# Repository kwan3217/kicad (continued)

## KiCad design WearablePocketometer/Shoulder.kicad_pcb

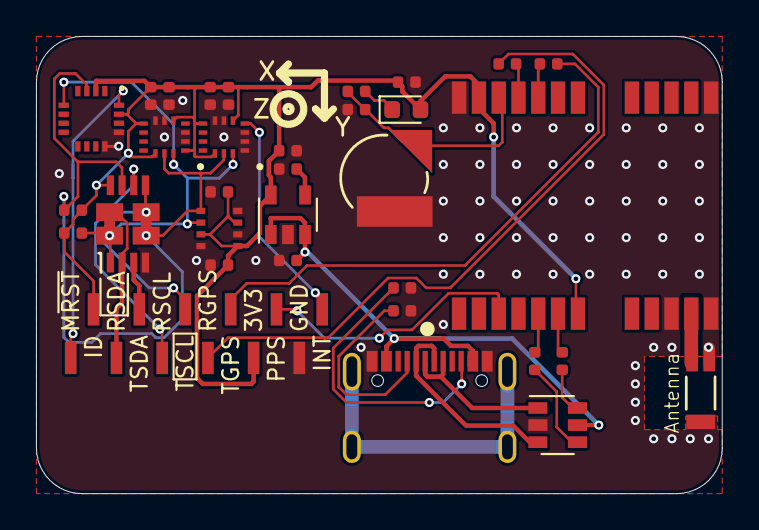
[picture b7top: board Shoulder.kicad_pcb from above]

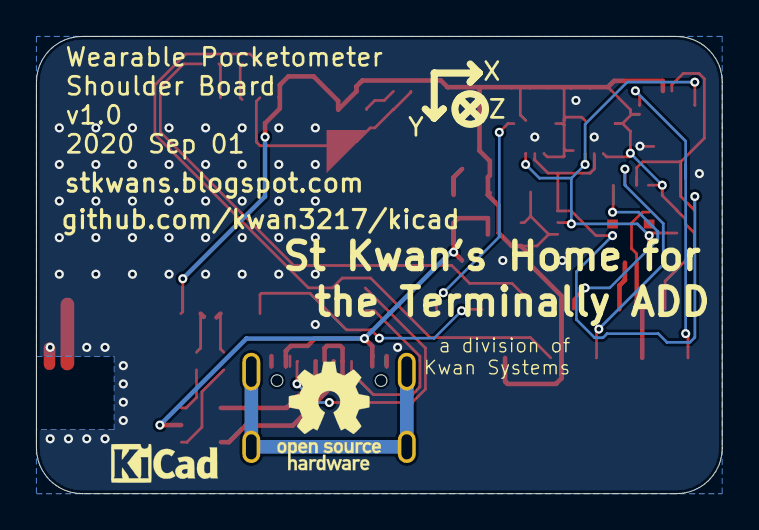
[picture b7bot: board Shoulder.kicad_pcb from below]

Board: 2 copper layers, 38.1 x 25.4 mm, 39 parts (3 on the bottom side), 28 nets.

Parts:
B601: ML414H; Coin_Cell_ML414H
C305, C308, C406, C408, C505, C508, C804: 100nF; C_0402_1005Metric
C601, C801: 1uF; C_0402_1005Metric
C805: 2.2uF; C_0402_1005Metric
D601: 0.5A/40V/420mV; D_0603_1608Metric
G504: Axis
G901: DesignedWithKicad; Symbol_KiCAD-Logo_CopperAndSilkScreenTop_small
G902: KwanSystems; StKwansSoldermask
G903: OSHW; OSHW-Logo_5.7x6mm_SilkScreen
J201, J207: SolderJumper_2_Open; SolderJumper-2_Bridged
J202: Conn_02x06_Male; PinSocket_1x12_P1.27mm_Vertical_SMD_Pin1Left
J701: USB_C_Receptacle_USB2.0; GCTUSBTypeC_PTH
R201, R207: 10k; R_0402_1005Metric
R602: 100k; R_0402_1005Metric
R603: 33; R_0402_1005Metric
R605, R606, R620, R621: 27; R_0402_1005Metric
R701, R702: 5.1k; R_0402_1005Metric
U201: AK09970
U202: P82B96; TSSOP-8_3x3mm_P0.65mm
U301, U501: LSM6DSO; LGA-14L
U401: BME280
U601: NEO_M8U; NEO-M9N_M8T_M8U
U701: USBLC6-2SC6; SOT-23-6
U801: MIC5319 3.3V; SOT-23-5
Y601: W3011

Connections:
+5V: C801.1, J701.A4, J701.A9, J701.B4, J701.B9, U701.5, U801.1, U801.3
/Shoulder/GPS/D+: R606.1, U701.6
/Shoulder/GPS/D-: R605.1, U701.4
/Shoulder/GPS/GPS_ANT1: U601.11, Y601.1
/Shoulder/GPS/R_D+: R606.2, U601.6
/Shoulder/GPS/R_D-: R605.2, U601.5
/Shoulder/GPS/Regulator/BYP: C804.1, U801.4
/Shoulder/GPS/USB/CC1: J701.A5, R701.1
/Shoulder/GPS/USB/CC2: J701.B5, R702.1
/Shoulder/GPS/USB/PD+: J701.A6, J701.B6, U701.1
/Shoulder/GPS/USB/PD-: J701.A7, J701.B7, U701.3
/Shoulder/GPS/V_BATT: B601.1, C601.1, R603.2, U601.22
/Shoulder/Q_3V3: C305.1, C308.1, C406.1, C408.2, C505.1, C508.1, C805.1, D601.2, J202.4, J202.11, R201.1, R207.1, R602.1, U201.2, U201.15, U202.8, U301.5, U301.8, U301.12, U401.2, U401.6, U401.8, U501.1, U501.5, U501.8, U501.12, U601.7, U601.23, U801.5
/Shoulder/Q_GND: B601.2, C305.2, C308.2, C406.2, C408.1, C505.2, C508.2, C601.2, C801.2, C804.2, C805.2, J202.2, J701.A1, J701.A12, J701.B1, J701.B12, R602.2, R701.2, R702.2, U201.12, U201.13, U202.4, U301.1, U301.2, U301.3, U301.6, U301.7, U401.1, U401.5, U401.7, U501.2, U501.3, U501.6, U501.7, U601.10, U601.12, U601.13, U601.24, U701.2, U801.2, Y601.2, Y601.3
/Shoulder/Q_INT: J202.1, U301.4
/Shoulder/Q_MAG~RST: J202.12, U201.16
/Shoulder/Q_PPS: J202.3, U601.3
/Shoulder/Q_RX_GPS: J202.6, R621.2
/Shoulder/Q_RX_SCL: J202.8, U202.6
/Shoulder/Q_RX_SDA: J201.2, J202.10, U202.2
/Shoulder/Q_TX_GPS: J202.5, R620.2
/Shoulder/Q_TX_SCL: J202.7, J207.2, U202.5
/Shoulder/Q_TX_SDA: J202.9, U202.3
/Shoulder/SCL: J207.1, R207.2, U201.3, U202.7, U301.13, U401.4, U501.13
/Shoulder/SDA: J201.1, R201.2, U201.5, U202.1, U301.14, U401.3, U501.14
unnamed: D601.1, R603.1
unnamed: R620.1, U601.20
unnamed: R621.1, U601.21

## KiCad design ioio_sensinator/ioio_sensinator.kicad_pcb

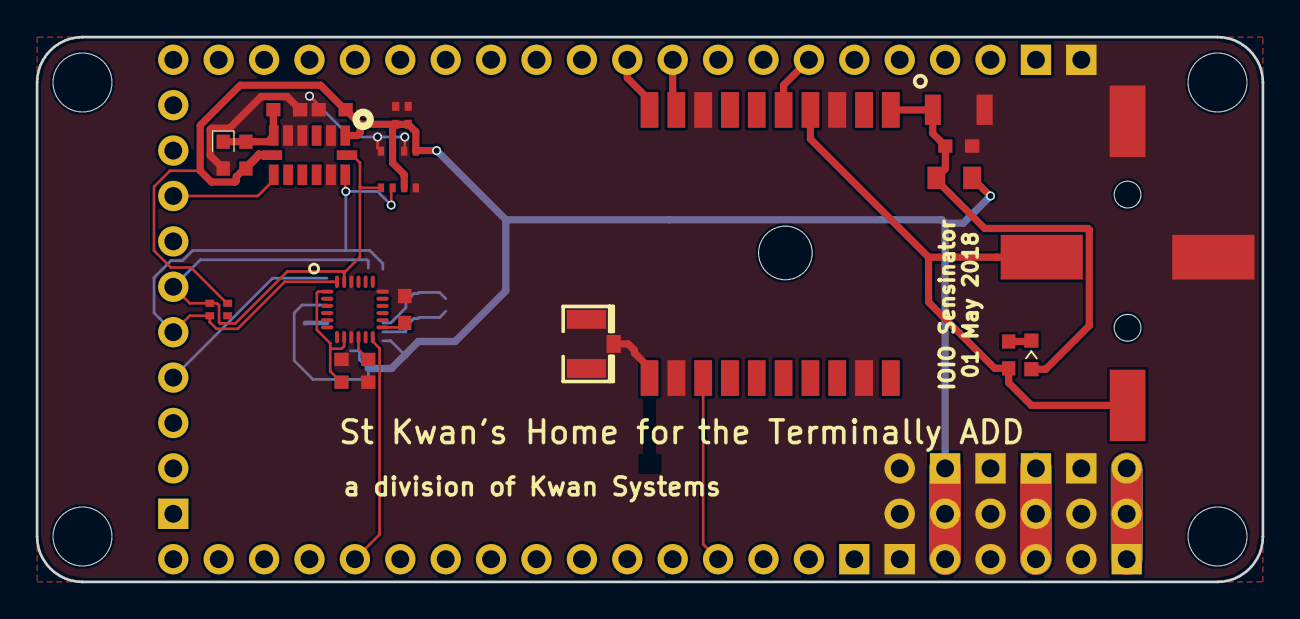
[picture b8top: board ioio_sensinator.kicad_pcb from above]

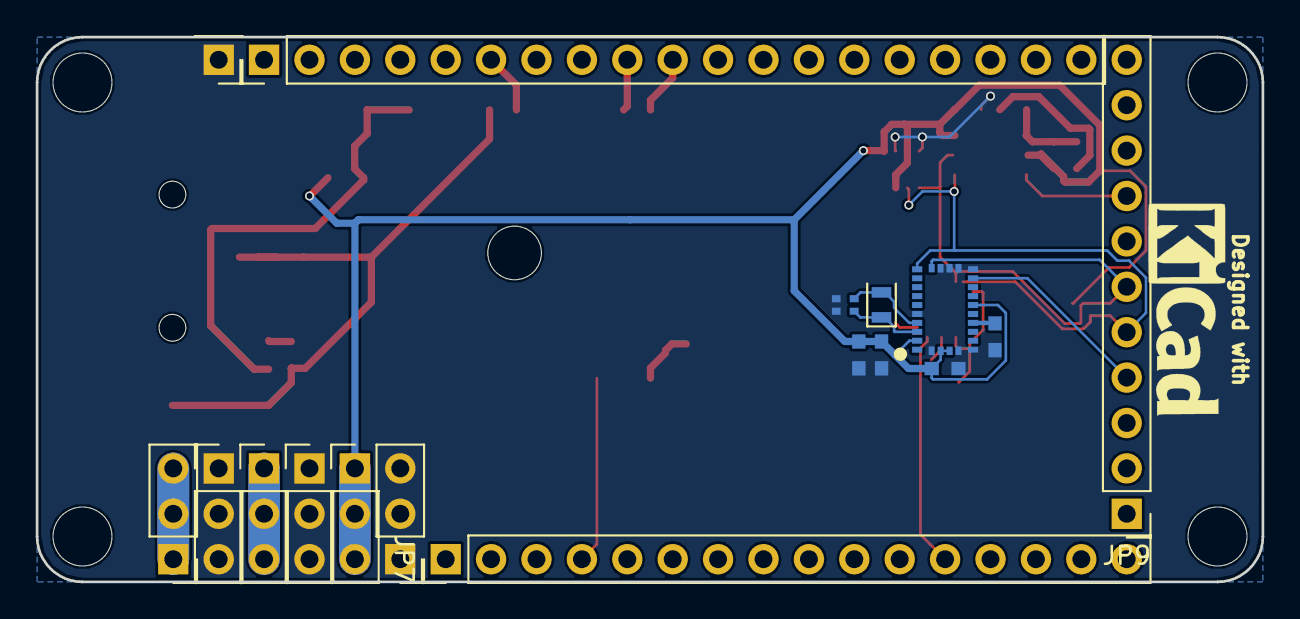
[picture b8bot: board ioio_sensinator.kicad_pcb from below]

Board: 2 copper layers, 68.6 x 30.5 mm, 38 parts (17 on the bottom side), 22 nets.

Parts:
B304: Coin_Cell; CR1220-2
C208, C210, C213, C301, C401, C405, C503, C509: 100nF; SMD_0603
C303: 10uF; SMD_1206
C304: 220mF; Supercap
C406: 10uF; SMD_0603_pol
C525: 120nF; SMD_0603
C526: 22pF; R_Array_Convex_2x0402
C528: 6.8nF; SMD_0603
C606: 100nF; R_Array_Convex_2x0402
D304: D_Schottky; D_0603
JP1, JP2, JP4, JP5, JP6, JP17: Conn_01x03; Pin_Header_Straight_1x03_Pitch2.54mm
JP3: Conn_01x01; Pin_Header_Straight_1x01_Pitch2.54mm
JP7: Conn_01x16; Pin_Header_Straight_1x16_Pitch2.54mm
JP9: Conn_01x11; Pin_Header_Straight_1x11_Pitch2.54mm
JP20: Conn_01x19; Pin_Header_Straight_1x19_Pitch2.54mm
L301: Ferrite; SMD_0805
R101: 4k7; R_Array_Convex_2x0402
R304: 10k; SMD_0603
R406: 100; SMD_0603
U201: MPU9250; QFN24_PAD
U301: FGPMMOPA6H
U401: ADXL375
U501: BNO055
U601: BME280
X311: uFL; U.FL
Y501: 32kiHz; Crystal_SMD_2012-2pin_2.0x1.2mm

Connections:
+3V3: C208.2, C213.2, C401.1, C503.2, C525.1, C528.1, C606.1, C606.2, JP2.1, JP2.2, JP2.3, L301.1, R101.1, R101.2, R406.1, U201.1, U201.8, U201.13, U401.1, U401.7, U501.3, U501.4, U501.11, U501.28, U601.2, U601.6, U601.8
+5V: JP4.1, JP4.2, JP4.3
+15V: JP1.1, JP1.2, JP1.3
/ADXL_INT: JP9.8, U401.8
/BNO055/CAP: C509.1, U501.9
/BNO055/XIN32: C526.1, U501.27, Y501.1
/BNO055/XOUT32: C526.2, U501.26, Y501.2
/BNO_INT: JP9.4, U501.14
/GPS_FIX: JP20.6, U301.5
/GPS_PPS: JP7.4, U301.13
/GPS_RX: JP20.10, U301.10
/GPS_TX: JP20.9, U301.9
/HighAcc/VS: C405.1, C406.1, R406.2, U401.6
/MPU9250/REGOUT: C210.2, U201.10
/MPU_INT: JP7.12, U201.12
/SCL: JP9.6, R101.3, U201.23, U401.14, U501.19, U601.4
/SDA: JP9.5, R101.4, U201.24, U401.13, U501.20, U601.3
/UltimateGPS/ANT: U301.11, X311.3
/UltimateGPS/VBACKUP: B304.+, C304.1, R304.1, U301.4
/UltimateGPS/VBACKUP+: D304.1, R304.2
/UltimateGPS/VGPS: C301.2, C303.2, D304.2, L301.2, U301.1
GND: B304.-, C208.1, C210.1, C213.1, C301.1, C303.1, C304.2, C401.2, C405.2, C406.2, C503.1, C509.2, C525.2, C526.3, C526.4, C528.2, C606.3, C606.4, JP3.1, JP5.1, JP5.2, JP5.3, JP6.1, JP6.2, JP6.3, JP17.1, JP17.2, JP17.3, U201.9, U201.18, U201.22, U301.3, U301.8, U301.12, U301.19, U401.2, U401.4, U401.5, U401.12, U501.2, U501.5, U501.6, U501.15, U501.16, U501.17, U501.18, U501.25, U601.1, U601.5, U601.7, X311.1, X311.2

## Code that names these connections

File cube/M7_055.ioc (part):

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Mcu.Name=STM32F722R(C-E)Tx
Mcu.Package=LQFP64
Mcu.UserName=STM32F722RETx
PA1.GPIOParameters=GPIO_Label
PA1.GPIO_Label=ADXL_INT
PA1.Signal=S_TIM2_CH2
PA10.GPIOParameters=GPIO_Label
PA10.GPIO_Label=M7_RX
PA10.Mode=Asynchronous
PA10.Signal=USART1_RX
PA11.GPIOParameters=GPIO_Label
PA11.GPIO_Label=D-
PA11.Mode=Device_Only
PA11.Signal=USB_OTG_FS_DM
PA12.GPIOParameters=GPIO_Label
PA12.GPIO_Label=D+
PA12.Mode=Device_Only
PA12.Signal=USB_OTG_FS_DP
PA15.GPIOParameters=GPIO_Label
PA15.GPIO_Label=BNO_INT
PA15.Signal=S_TIM2_CH1_ETR
PA2.GPIOParameters=GPIO_Label
PA2.GPIO_Label=GPS_PPS
PA2.Signal=S_TIM2_CH3
PA3.GPIOParameters=GPIO_Label
PA3.GPIO_Label=GPS_FIX
PA3.Signal=S_TIM2_CH4
PA9.GPIOParameters=GPIO_Label
PA9.GPIO_Label=M7_TX
PA9.Mode=Asynchronous
PA9.Signal=USART1_TX
PB10.GPIOParameters=GPIO_Label
PB10.GPIO_Label=GPS_RX
PB10.Mode=Asynchronous
PB10.Signal=USART3_TX
PB11.GPIOParameters=GPIO_Label
PB11.GPIO_Label=GPS_TX
PB11.Mode=Asynchronous
PB11.Signal=USART3_RX
PB3.GPIOParameters=GPIO_Label
PB3.GPIO_Label=SCK
PB3.Mode=Full_Duplex_Master
PB3.Signal=SPI1_SCK
PB4.GPIOParameters=GPIO_Label
PB4.GPIO_Label=MISO
PB4.Mode=Full_Duplex_Master
PB4.Signal=SPI1_MISO
PB5.GPIOParameters=GPIO_Label
PB5.GPIO_Label=MOSI
PB5.Mode=Full_Duplex_Master
PB5.Signal=SPI1_MOSI
PB6.GPIOParameters=GPIO_Label,GPIO_FM8
PB6.GPIO_FM8=SYSCFG_PMC_I2C_PB8_FMP
PB6.GPIO_Label=SCL
PB6.Mode=I2C
PB6.Signal=I2C1_SCL
PB7.GPIOParameters=GPIO_Label,GPIO_FM7
PB7.GPIO_FM7=SYSCFG_PMC_I2C_PB7_FMP
PB7.GPIO_Label=SDA
PB7.Mode=I2C
PB7.Signal=I2C1_SDA
PC6.GPIOParameters=GPIO_Label
PC6.GPIO_Label=PWMR
PC6.Signal=S_TIM3_CH1
PC7.GPIOParameters=GPIO_Label
PC7.GPIO_Label=PWMG
PC7.Signal=S_TIM3_CH2
PC8.GPIOParameters=GPIO_Label
PC8.GPIO_Label=PWMB
PC8.Signal=S_TIM3_CH3
PC9.GPIOParameters=GPIO_Label
PC9.GPIO_Label=PWM4
PC9.Signal=S_TIM3_CH4
PD2.GPIOParameters=GPIO_Label
PD2.GPIO_Label=CS
PD2.Signal=GPIO_Output
PH0-OSC_IN.GPIOParameters=GPIO_Label
PH0-OSC_IN.GPIO_Label=XIN
PH0-OSC_IN.Mode=HSE-External-Oscillator
PH0-OSC_IN.Signal=RCC_OSC_IN
PH1-OSC_OUT.GPIOParameters=GPIO_Label
PH1-OSC_OUT.GPIO_Label=XOUT
PH1-OSC_OUT.Mode=HSE-External-Oscillator
PH1-OSC_OUT.Signal=RCC_OSC_OUT
RCC.HSE_VALUE=16000000
RCC.SYSCLKFreq_VALUE=120000000
RCC.SYSCLKSource=RCC_SYSCLKSOURCE_PLLCLK

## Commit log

2017-03-04 Initial import of Naninator
2017-03-06 Routed the Naninator, except for two tracks
2017-03-06 One or two ground connections are left
2017-03-06 Added Kwan Circle, and finished routing of Naninator
2017-03-06 Added Kwan Circle
2017-03-07 Started RocketometerM4, using a CortexM4 in a LQFP64 package
2017-03-08 Added MicroSD socket
2017-03-09 Added switch footprint
2017-03-09 Started M4 evaluation board
2017-03-10 Starting on CortexM7-based design
2017-04-24 Adding Tomo
2017-04-24 Adding GPS and starting layout on Tomo
2017-04-25 Continuing layout of Tomo
2017-04-26 Starting to decorate
2017-04-26 Added several 3d models
2017-04-27 adding spi comnections so that arduino bootloader can be installed
2017-04-30 Consolidated Tomo and Encoder into one folder
2017-05-01 Adding BOM submodule
2017-05-01 Added Digikey part numbers
2017-05-01 Added Digikey part numbers to parts
2017-05-02 Put other sensors on the board
2017-05-03 continuing to add more sensors
2017-05-04 Put both USB sockets on the same side, so I can choose which to populate. There is no clearance under the board, so don't put the big socket there.
2017-05-04 Ready to try adding supercap
2017-05-04 Adding supercap
2017-05-06 Committing so I can switch back to master
2017-05-08 Broke the schematic down to a bunch of subsheets
2017-06-28 Added footprints to plug FeatherWing and Nano directly into Tomo
2017-06-28 Made a plugin version of Tomo
2017-06-30 More changes
2017-06-30 Label changes
2017-07-03 Removed KiCad_BOM_Wizard. As that was the file causing the nullsha1 problem, hopefully this fixes it
2017-07-03 Redid encoder to use RP2 parts
2017-07-07 Moved 4 of 5 lights to one corner of the board
2017-07-10 Files as ordered
2017-07-10 Broke Arduino into ATMega part. Fixed PPS and FIX pins
2017-07-11 Consistentized the Naninator, Tomo, and Tomo Plugin
2017-07-12 Removed extraneous silkscreen from GPS module
2017-07-12 Change in EELAYER (Different Kicad version?)
2017-07-12 Removed some extraneous silkscreen, changed some footprints to KwanSystems library
2017-07-18 Adding kwire stuff
2017-07-19 Added 1-bit adder driver and control/indicator parts to library
2017-07-19 Put source files for models into proper subfolders
2017-07-19 Added addsub modules, which can do subtraction if you set the SUB input and carry_in inputs appropriately
2017-07-21 Tomo soldermask fix, adding kwire stuff
2017-07-22 Added xordriver, to test xor gate in kwire
2017-07-22 Removing files which got moved to Python Kwire project
2017-07-24 Rework to solve solder mask problem and use 1206 parts
2017-08-04 Added Tomo-pHAT
2017-08-04 Removing extraneous stuff from HAT folder
2017-08-04 Added stuff
2017-08-05 Setting up Tomo Hat
2017-08-07 Adding Loginator (port from Eagle)
2017-08-07 Loginator schematic and board are now consistent
2017-08-08 Consistent board and schematic, which passes ERC and DRC
2017-08-08 Fixed backwards pin issue on current sensor, combined some resistors into arrays, fixed inherited error in USB resistors
2017-08-08 Starting Tracker pHAT - will have a GPS and all the sensors I can cram on it
2017-08-08 Added project file for tracker pHat
2017-08-08 Moved sensors to their own folder, did work on Tracker pHat
2017-08-09 Imported Adafruit BNO055 breakout
2017-08-10 Importing Rocketometer6050 as flown
2017-08-10 Two "unconnected" airwires left. One is a ground connection which is actually through the case of the SD card, the other is through the case of the USB plug
2017-08-10 being careful with documentation
2017-08-10 Worked on Rocketometer055
2017-08-11 More work on Rocketometer055
2017-08-11 First complete routing of Rocketometer
2017-08-11 Bug fix to handle case where there is no footprint
2017-08-13 Modular hardware, just before redoing the main board
2017-08-13 Finished baseline routing of second version of Rocketometer055
2017-08-14 Bookkeeping changes
2017-08-14 Started Rocketometer055 pHAT
2017-10-16 Commit for merge
2017-10-16 Started placing parts on Yukari6 hat
2017-10-16 Made a blocks directory. Right now it has the USB/charger/regulator chain
2017-10-17 Working on Rocketometer055
2017-10-23 Made YukariWheel, a robot controller designed to go in place of the encoder board
2017-10-25 Starting on YukariWheel
2017-10-25 More work on YukariWheel
2017-10-25 Started layout on YukariWheel
2017-10-25 More layout of YukariWheel
2017-10-26 Continuing layout of YukariWheel
2017-11-03 More work on Loginator
2018-01-02 Added Adafruit Eagle BNO055
2018-01-02 Added import of Adafruit BNO055
2018-01-02 Removed Adafruit markings
2018-01-03 Started M7_055, a rocketometer built around an STM32F7 and a BNO055
2018-01-03 Starting to add labels to STM32F
2018-01-03 Committing for merge
2018-01-03 More work on M7_055
2018-01-04 Added M7 breakout board
2018-01-05 Assigned pins
2018-01-06 Added correct version of IOC
2018-01-08 Pushing
2018-01-08 Added smaller SPDT switch
2018-01-09 Baseline routing completed
2018-04-18 Starting IOIO_Sensinator
2018-04-18 More work on IOIO sensinator
2018-04-18 Starting to lay out IOIO_Sensinator
2018-04-18 More wiring of ioio_sensinator
2018-04-18 Adding standoff
2018-09-08 Updated stuff to KiCad 5
2019-04-16 Adding Loginator_Pihat. To begin with, it will be a clone of the Rocketometer6050. It will then be updated with a type C plug and updated sensors.
2019-08-21 Adding Precision 2.0, the pure-Kicad, Python-routed next version of Project Precision
2019-08-21 Adding parts needed by Precision 2.0
2019-08-21 Added Charlieplex traces. The bulk was done with CharlieplexTraces.py, with quite a bit of hand-optimization afterwards
2019-08-21 Removed Precision1.1 stuff from this folder
2019-08-21 Updating Kicad version of sheets
2019-08-21 Removed pycache from git
2019-08-21 Removed kicad cache stuff
2019-08-21 Finished connecting all signals, added buttons for setting time
2019-08-23 Moved manual set buttons to the GPS TX/RX lines
2019-10-14 Starting SensorFeatherWing
2020-08-28 Adding WearablePocketometer as-ordered for Shoulder and Shoe boards
2020-08-28 Added Ponoko files
2020-10-15 Files used to build steel stencil and pocket board, 2020-Oct-09
2020-10-21 Create LICENSE
2021-09-28 Refactored Kwan Systems library, ready to split to new repository
2021-09-28 Removed kwan_kicad_lib, ready for subtree
